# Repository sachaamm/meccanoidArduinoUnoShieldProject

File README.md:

## Meccanoid Personnal Robot Arduino PROJECT

### Overview

https://www.youtube.com/watch?v=WydUIxD037A

### Hardware

This is the hardware used on this project
- Arduino Esplora controller ( [available here](https://fr.shopping.rakuten.com/offer/buy/2201571401/gratuit-esplora-rocker-game-board-atmega32u4-module-support-robot-ecran-lcd-1-8-pouces-tft.html?bbaid=2974341335&t=180112&xtatc=PUB-%5Bggp%5D-%5BInformatique%5D-%5BAccessoires%5D-%5B2201571401%5D-%5Bneuf%5D-%5BYOINS%5D&ptnrid=pt%7C89152206803%7Cc%7C53434268603%7C2201571401&ptnrid=s24llCvmK_dc|pcrid|53434268603|pkw||pmt|&ja2=tsid:67590|cid:285670043|agid:14467128323|tid:aud-269143871707:pla-89152206803|crid:53434268603|nw:g|rnd:16272168161431935316|dvc:c|adp:1o1&gclid=Cj0KCQiAm5viBRD4ARIsADGUT25t6cqBpQwFY6DI_-hoSrfeVMcB9rYTRa3jL_OBDdxffjhCL8IMMwQaAhTVEALw_wcB) )
- 2x HM10 Bluetooth ( [available here](https://fr.shopping.rakuten.com/offer/buy/2552517283/bluetooth-4-0-pour-arduino-android-ios-hm-10-ble-cc2540-cc2541-serie-sans-fil-module.html?bbaid=3825848571&t=180176&xtatc=PUB-%5Bggp%5D-%5BInformatique%5D-%5BAccessoires%5D-%5B2552517283%5D-%5Bneuf%5D-%5BBuyCool%5D&ptnrid=pt%7C412904372812%7Cc%7C248309744840%7C2552517283&ptnrid=snHX2pR89_dc|pcrid|248309744840|pkw||pmt|&ja2=tsid:|cid:723021248|agid:58346345904|tid:aud-329787467942:pla-412904372812|crid:248309744840|nw:g|rnd:14070458870104494051|dvc:c|adp:1o1&gclid=Cj0KCQiAm5viBRD4ARIsADGUT24Wg6h3EPiis6JnYEjRWdm48go2qsXzKBhFZeI0HbhM2KkK3keFkXkaAp33EALw_wcB) )
- 2x Arduino UNO ( Eelego UNO ) ( [available here](https://fr.farnell.com/arduino-org/a000073/arduino-uno-cms-kit-de-dev/dp/2285200?gclid=Cj0KCQiAm5viBRD4ARIsADGUT27SB2p4XF8JkJ1D9ywi_7TdR8JGiINMsCUoFB-QVbYXcGUIP6FpGJEaAtopEALw_wcB&gross_price=true&mckv=nAfw6jTY_dc|pcrid|80993927942|&CAWELAID=120185620000343524&CAGPSPN=pla&CAAGID=13038120062&CMP=KNC-GFR-GEN-SHOPPING-2285200&CATCI=aud-127173563342:pla-89203456717) )
- 1x FourRelay-5V module ( [available here](https://www.banggood.com/fr/5V-4-Channel-Relay-Module-For-Arduino-PIC-ARM-DSP-AVR-MSP430-Blue-p-87987.html?gmcCountry=FR&currency=EUR&createTmp=1&utm_source=googleshopping&utm_medium=cpc_union&utm_content=2zou&utm_campaign=ssc-fr-all&gclid=Cj0KCQiAm5viBRD4ARIsADGUT25e2Ajjgxh5M218oXJrrltuOxtD6GfLqWbmM2E8d8yZ26lLdXyDNQsaAtivEALw_wcB&cur_warehouse=HK) )
- 1x FTDI Chip ( [available here](https://fr.banggood.com/FTDI-USB-OSD-Programmer-Module-for-F3-Flight-Control-AIO-Transmitter-OSD-BEC-Current-Sensor-p-1111287.html?akmClientCountry=FR&gmcCountry=FR&currency=EUR&createTmp=1&utm_source=googleshopping&utm_medium=cpc_bgcs&utm_content=zouzou&utm_campaign=pla-frg-toys-rctoys-pc&cur_warehouse=CN) )
- 1x 5V supply for Arduino B
- Wires / connector  / etc...

### Installation 
- Install Meccanoid Arduino Library ( [provided on this link](http://www.meccano.com/meccanoid-opensource) )
- Set up your Bluetooth slave-master pairing with an FTDI chip. One device will be Master and the other will be slave.
( [check this link](https://www.instructables.com/id/How-to-Use-Bluetooth-40-HM10/?fbclid=IwAR2GLLHkLqt9dNQLBvCo8Qc5vnz0IyvcvLNwDCA6tnjOxEIhA4G5cf7OB1w) )
- Upload the Arduino Source code on your devices, included in this repository in **Arduino/** 

   **EsploraBT3/** is for Esplora Controller
   
   **ReceiveBTEsplora_ArduinoRelay/** is for Arduino A
   
   **ReceiveBTESplora_Servos/** is for Arduino B
  
- Connect wires and devices following the schematic picture for your 2 Arduino and your HM10 device

- Connect HM10 master bluetooth device to your Esplora controller following this picture 

### Instructions

- **Do not connect Meccanoid 5V supply GND to your Arduino B GND**, you will get a short-circuit on your HM10 bluetooth device which may destroy your device.
- **Do not upload your Arduino code when HM10-Serial connection is occuring** ( on the Arduino A, the HM10 device is connected to the Serial ports,
DIGITAL 0 (RX) and DIGITAL 1 (TX). 
- You may plug your motors to the HBridge in a different way than mine. If you get a mismatch on instructions directions, you can edit the Arduino B Code ( **ReceiveBTEsplora_ArduinoRelays** )
- Provide another 5V supply to your Arduino A using the USB port, because this device is controlling relays on a circuit supplied by the Meccanoid 5V supply, we have to supply this Arduino to another current source to avoid short circuits on the HBridge feet motors.

### Develop

- You can edit your own animations by editing the Arduino A Code ( **ReceiveBTEsplora_Servos** )

### STL Files

2 stl files for 3D printing are provided in order to grab easily your Esplora controller on hands

# Have Fun !

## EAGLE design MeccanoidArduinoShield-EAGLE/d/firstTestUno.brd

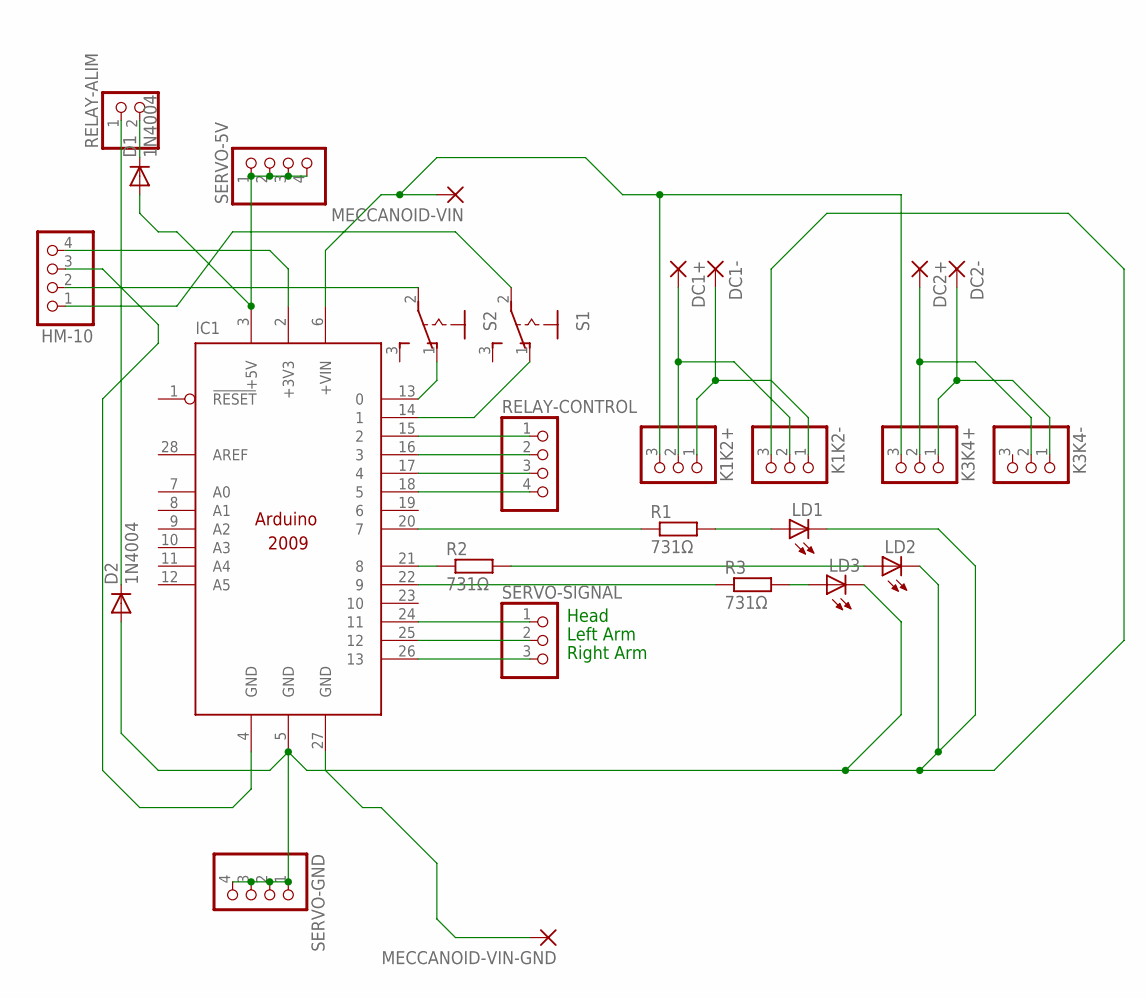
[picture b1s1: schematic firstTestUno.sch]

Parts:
D1, D2: 1N4004; DO41-10; MPN 1N4004+
DC1+, DC1-, DC2+, DC2-: 1,6/0,8; MPN TK20-1,6/0,8-PVDF-CL
HM-10: PINHD-1X4; 1X04
IC1: ARDUINO2009_10; ARDUINO2009
K1K2+, K1K2-, K3K4+, K3K4-: PINHD-1X3/90; 1X03/90
LD1, LD2, LD3: LED3MM; MPN LED 2F
MECCANOID-VIN: 1,6/0,8; MPN TK20-1,6/0,8-PVDF-CL
MECCANOID-VIN-GND: 1,6/0,8; MPN TK20-1,6/0,8-PVDF-CL
R1, R2, R3: 731Ω; 0207/5V; MPN 74270035
RELAY-ALIM: PINHD-1X2; 1X02; MPN B65659F0001X023
RELAY-CONTROL: PINHD-1X4; 1X04
S1, S2: 255SB; MPN CA3106E32-55SB03
SERVO-5V: PINHD-1X4; 1X04
SERVO-GND: PINHD-1X4; 1X04
SERVO-SIGNAL: PINHD-1X3; 1X03; MPN V23234A0001X038-EV-144

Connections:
unnamed: HM-10.3, IC1.4 (GND)
unnamed: HM-10.4, IC1.2 (+3V3)
unnamed: IC1.13 (0), S2.1 (O)
unnamed: D1.A, IC1.3 (+5V), SERVO-5V.1, SERVO-5V.2, SERVO-5V.3, SERVO-5V.4
unnamed: HM-10.2, S2.2
unnamed: D1.C, RELAY-ALIM.2
unnamed: IC1.27 (GND), MECCANOID-VIN-GND.1
unnamed: IC1.26 (13), SERVO-SIGNAL.3
unnamed: IC1.25 (12), SERVO-SIGNAL.2
unnamed: IC1.24 (11), SERVO-SIGNAL.1
unnamed: IC1.15 (2), RELAY-CONTROL.1
unnamed: IC1.16 (3), RELAY-CONTROL.2
unnamed: IC1.17 (4), RELAY-CONTROL.3
unnamed: IC1.18 (5), RELAY-CONTROL.4
unnamed: D2.C, RELAY-ALIM.1
unnamed: IC1.20 (7), R1.1
unnamed: DC1+.1, K1K2+.2, K1K2-.2
unnamed: IC1.14 (1), S1.1 (O)
unnamed: HM-10.1, S1.2
unnamed: LD1.A, R1.2
unnamed: DC1-.1, K1K2+.1, K1K2-.1
unnamed: LD2.A, R2.2
unnamed: LD3.A, R3.2
unnamed: IC1.22 (9), R3.1
unnamed: IC1.21 (8), R2.1
unnamed: DC2+.1, K3K4+.2, K3K4-.2
unnamed: DC2-.1, K3K4+.1, K3K4-.1
unnamed: IC1.6 (+VIN), K1K2+.3, K3K4+.3, MECCANOID-VIN.1
unnamed: D2.A, IC1.5 (GND), K1K2-.3, LD1.K (C), LD2.K (C), LD3.K (C), SERVO-GND.1, SERVO-GND.2, SERVO-GND.3, SERVO-GND.4

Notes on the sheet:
Left Arm
Right Arm
Head

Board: 2 copper layers, 27 parts (0 on the bottom side), 29 nets, no tracks yet.

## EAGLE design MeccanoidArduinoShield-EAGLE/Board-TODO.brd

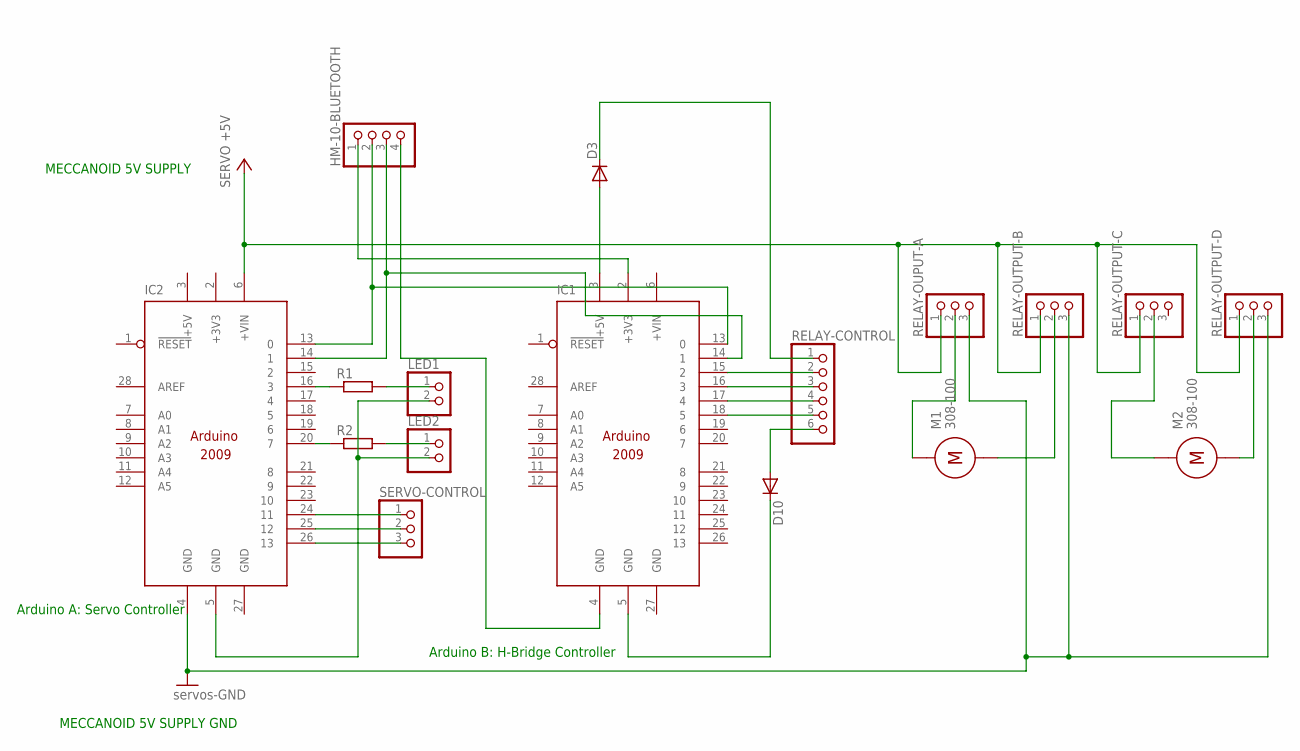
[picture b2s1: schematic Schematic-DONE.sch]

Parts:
D3, D10: 1N4148DO35-7; DO35-7
HM-10-BLUETOOTH: PINHD-1X4; 1X04
IC1, IC2: ARDUINO2009_10; ARDUINO2009
LED1, LED2: PINHD-1X2; 1X02
M1, M2: 308-100
R1, R2: R-EU_0204/2V; 0204V
RELAY-CONTROL: PINHD-1X6; 1X06
RELAY-OUPUT-A: PINHD-1X3; 1X03
RELAY-OUTPUT-B: PINHD-1X3; 1X03
RELAY-OUTPUT-C: PINHD-1X3; 1X03
RELAY-OUTPUT-D: PINHD-1X3; 1X03
SERVO-CONTROL: PINHD-1X3; 1X03

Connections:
+3V3: IC2.2 (+3V3)
+5V: IC2.3 (+5V), IC2.6 (+VIN), RELAY-OUPUT-A.1, RELAY-OUTPUT-B.1, RELAY-OUTPUT-C.1, RELAY-OUTPUT-D.1; also elsewhere on the board
GND: IC1.27 (GND), IC2.4 (GND), IC2.27 (GND), RELAY-OUPUT-A.3, RELAY-OUTPUT-B.3, RELAY-OUTPUT-D.3
unnamed: M1.POS, RELAY-OUPUT-A.2
unnamed: M2.POS, RELAY-OUTPUT-C.2
unnamed: D3.C, RELAY-CONTROL.1
unnamed: IC1.15 (2), RELAY-CONTROL.2
unnamed: IC1.16 (3), RELAY-CONTROL.3
unnamed: IC1.17 (4), RELAY-CONTROL.4
unnamed: IC1.18 (5), RELAY-CONTROL.5
unnamed: D3.A, IC1.3 (+5V)
unnamed: IC2.16 (3), R1.1
unnamed: M1.NEG, RELAY-OUTPUT-B.2
unnamed: IC2.24 (11), SERVO-CONTROL.1
unnamed: D10.C, IC1.5 (GND)
unnamed: IC2.25 (12), SERVO-CONTROL.2
unnamed: IC2.26 (13), SERVO-CONTROL.3
unnamed: HM-10-BLUETOOTH.1, IC1.2 (+3V3)
unnamed: D10.A, RELAY-CONTROL.6
unnamed: HM-10-BLUETOOTH.2, IC1.13 (0), IC2.13 (0)
unnamed: HM-10-BLUETOOTH.4, IC1.4 (GND)
unnamed: HM-10-BLUETOOTH.3, IC1.14 (1), IC2.14 (1)
unnamed: LED1.1, R1.2
unnamed: IC2.5 (GND), LED1.2, LED2.2
unnamed: LED2.1, R2.2
unnamed: IC2.20 (7), R2.1
RELAY-OUTPUT-D: M2.NEG, RELAY-OUTPUT-D.2

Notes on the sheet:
MECCANOID 5V SUPPLY
MECCANOID 5V SUPPLY GND
Arduino A: Servo Controller
Arduino B: H-Bridge Controller

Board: 2 copper layers, 18 parts (0 on the bottom side), 26 nets, no tracks yet.

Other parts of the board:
D1: DO35-7

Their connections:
+5V: D1.A, D1.C; also elsewhere on the board

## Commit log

2018-11-28 Add content
2018-11-28 gitignore
2018-11-28 remove gitignore as txt file and .idea
2019-01-11 based on L293D chip
2019-01-11 Commit to merge EsploraBT3
2019-01-11 Fix merge conflicts
2019-01-22 Update content for youtube video
2019-02-20 Meccanoid v3 : pwm hbridge with npn
